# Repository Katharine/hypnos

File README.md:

Project Hypnos
==============

A hardware controller for the Eight Sleep sleep mattress - because controlling your bed with a phone is a pain.

Turn a knob to adjust the temperature, press the knob to turn it on or off, or to turn off the alarm. Simple!

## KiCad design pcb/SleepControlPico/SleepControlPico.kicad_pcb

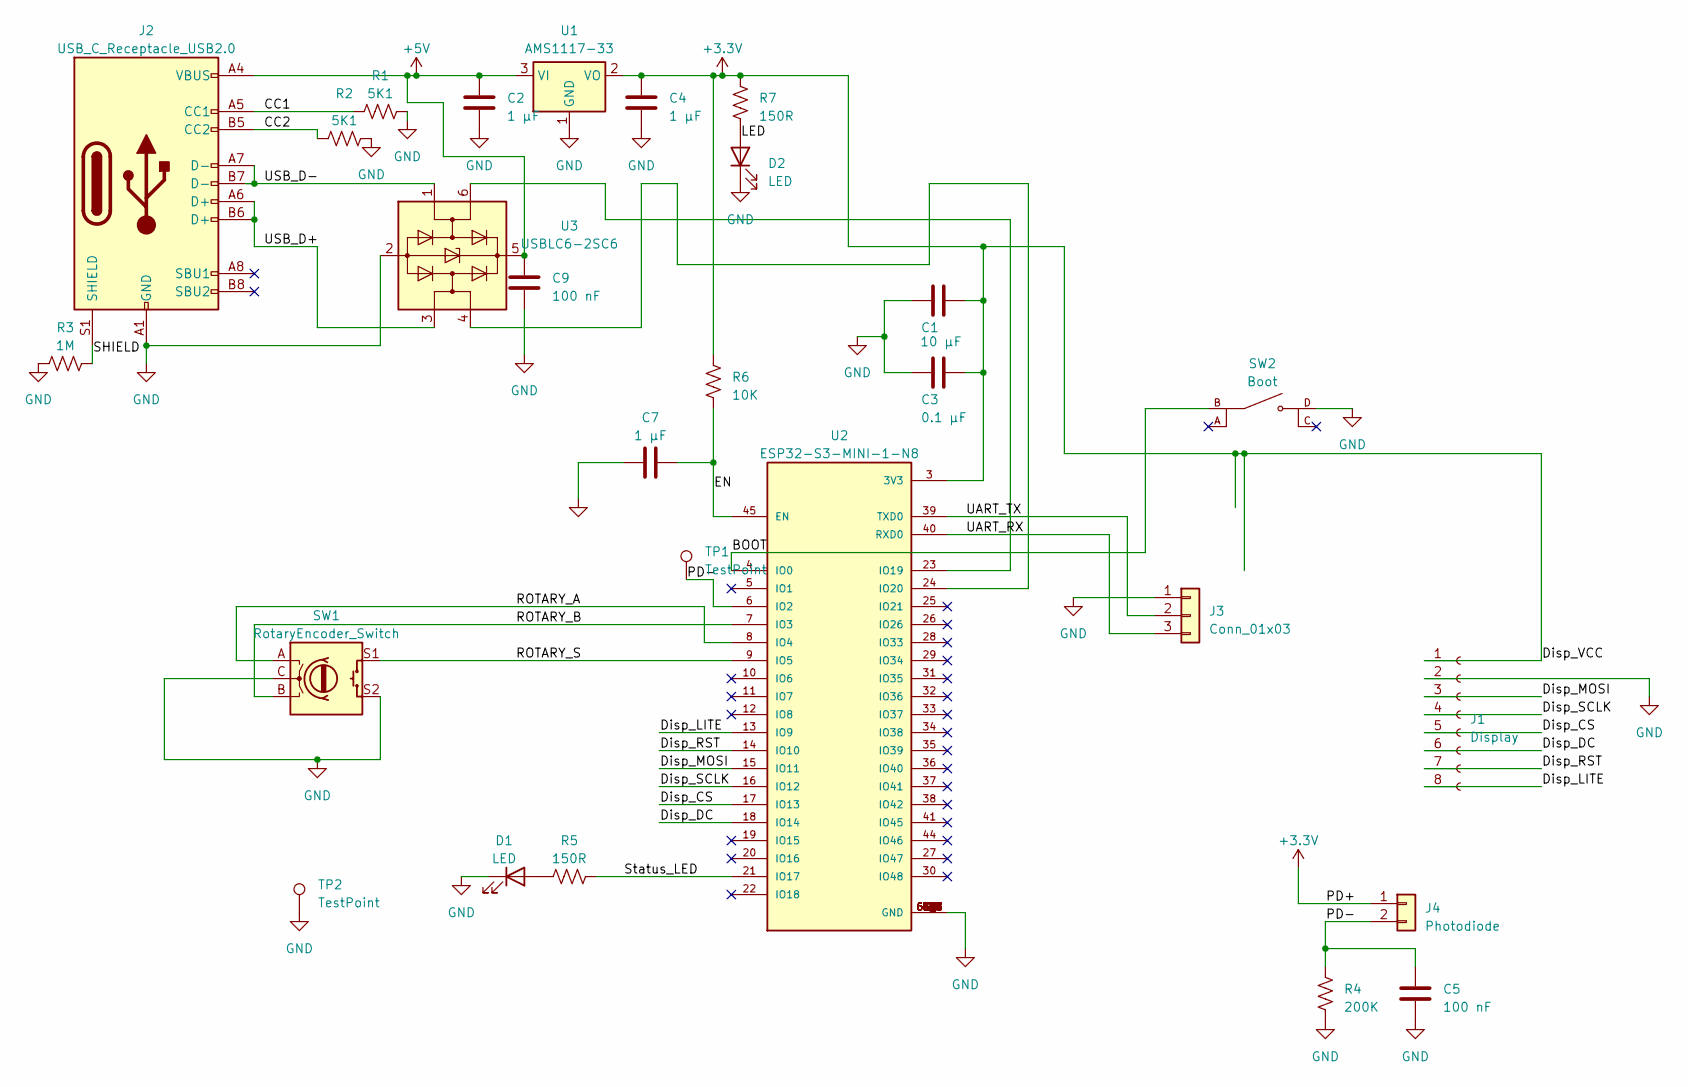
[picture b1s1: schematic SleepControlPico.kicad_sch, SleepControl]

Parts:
C1: 10 µF; C_0603_1608Metric; LCSC Part # C96446
C2, C4, C7: 1 µF; C_0402_1005Metric; LCSC Part # C52923
C3: 0.1 µF; C_0402_1005Metric; LCSC Part # C307331
C5, C9: 100 nF; C_0402_1005Metric; LCSC Part # C307331
D1, D2: LED; LED_0603_1608Metric; LCSC Part # C2286
J1: Display; JST-B8B-ZR-0; LCSC Part # C493145
J2: USB_C_Receptacle_USB2.0; USB_C_Receptacle_G-Switch_GT-USB-7010ASV; LCSC Part # C2988369
J3: Conn_01x03; PinHeader_1x03_P2.54mm_Horizontal; LCSC Part # C2935928
J4: Photodiode; JST_PH_B2B-PH-K_1x02_P2.00mm_Vertical; LCSC Part # C131337
R1, R2: 5K1; R_0603_1608Metric; LCSC Part # C23186
R3: 1M; R_0603_1608Metric; LCSC Part # C22935
R4: 200K; R_Axial_DIN0207_L6.3mm_D2.5mm_P7.62mm_Horizontal; LCSC Part # C58614
R5: 150R; R_0402_1005Metric; LCSC Part # C25133
R6: 10K; R_0603_1608Metric; LCSC Part # C25804
R7: 150R; R_0402_1005Metric; LCSC Part # C25082
SW1: RotaryEncoder_Switch; Bourns-PEC11R-4020F-S0012-MFG; LCSC Part # C143790
SW2: Boot; SW_TS-1187A-B-A-B; PARTREV A0; LCSC Part # C318884
TP1, TP2: TestPoint; TestPoint_Pad_D1.0mm
U1: AMS1117-33; SOT-223-3_TabPin2; LCSC Part # C6186
U2: ESP32-S3-MINI-1-N8; XCVR_ESP32-S3-MINI-1-N8; PARTREV v0.6; LCSC Part # C2913206
U3: USBLC6-2SC6; SOT-23-6; LCSC Part # C7519

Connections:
+3.3V: C1.1, C3.1, C4.1, J1.1, J4.1, R6.1, R7.1, U1.2 (VO), U2.3 (3V3)
+5V: C2.1, C9.2, J2.A4 (VBUS), J2.A9 (VBUS), J2.B4 (VBUS), J2.B9 (VBUS), U1.3 (VI), U3.5 (VBUS)
/BOOT: SW2.B, U2.4 (IO0)
/CC1: J2.A5 (CC1), R1.1
/CC2: J2.B5 (CC2), R2.1
/Disp_CS: J1.5, U2.17 (IO13)
/Disp_DC: J1.6, U2.18 (IO14)
/Disp_LITE: J1.8, U2.13 (IO9)
/Disp_MOSI: J1.3, U2.15 (IO11)
/Disp_RST: J1.7, U2.14 (IO10)
/Disp_SCLK: J1.4, U2.16 (IO12)
/EN: C7.2, R6.2, U2.45 (EN)
/PD-: C5.2, J4.2, R4.1, TP1.1, U2.6 (IO2)
/ROTARY_A: SW1.A, U2.8 (IO4)
/ROTARY_B: SW1.B, U2.7 (IO3)
/ROTARY_S: SW1.S1, U2.9 (IO5)
/SHIELD: J2.S1 (SHIELD), R3.1
/Status_LED: R5.2, U2.21 (IO17)
/UART_RX: J3.3, U2.40 (RXD0)
/UART_TX: J3.2, U2.39 (TXD0)
/USB_D+: J2.A6 (D+), J2.B6 (D+), U3.3 (I/O2)
/USB_D-: J2.A7 (D-), J2.B7 (D-), U3.1 (I/O1)
GND: C1.2, C2.2, C3.2, C4.2, C5.1, C7.1, C9.1, D1.1 (K), D2.1 (K), J1.2, J2.A1 (GND), J2.A12 (GND), J2.B1 (GND), J2.B12 (GND), J3.1, R1.2, R2.2, R3.2, R4.2, SW1.C, SW1.S2, SW2.D, TP2.1, U1.1 (GND), U2.1 (GND), U2.2 (GND), U2.42 (GND), U2.43 (GND), U2.46 (GND), U2.47 (GND), U2.48 (GND), U2.49 (GND), U2.50 (GND), U2.51 (GND), U2.52 (GND), U2.53 (GND), U2.54 (GND), U2.55 (GND), U2.56 (GND), U2.57 (GND), U2.58 (GND), U2.59 (GND), U2.60 (GND), U2.61 (GND), U2.61_1 (GND), U2.61_2 (GND), U2.61_3 (GND), U2.61_4 (GND), U2.61_5 (GND), U2.61_6 (GND), U2.61_7 (GND), U2.61_8 (GND), U2.62 (GND), U2.63 (GND), U2.64 (GND), U2.65 (GND), U3.2 (GND)
unnamed: D1.2 (A), R5.1
unnamed: D2.2 (A), R7.2
unnamed: U2.23 (IO19), U3.6 (I/O1)
unnamed: U2.24 (IO20), U3.4 (I/O2)

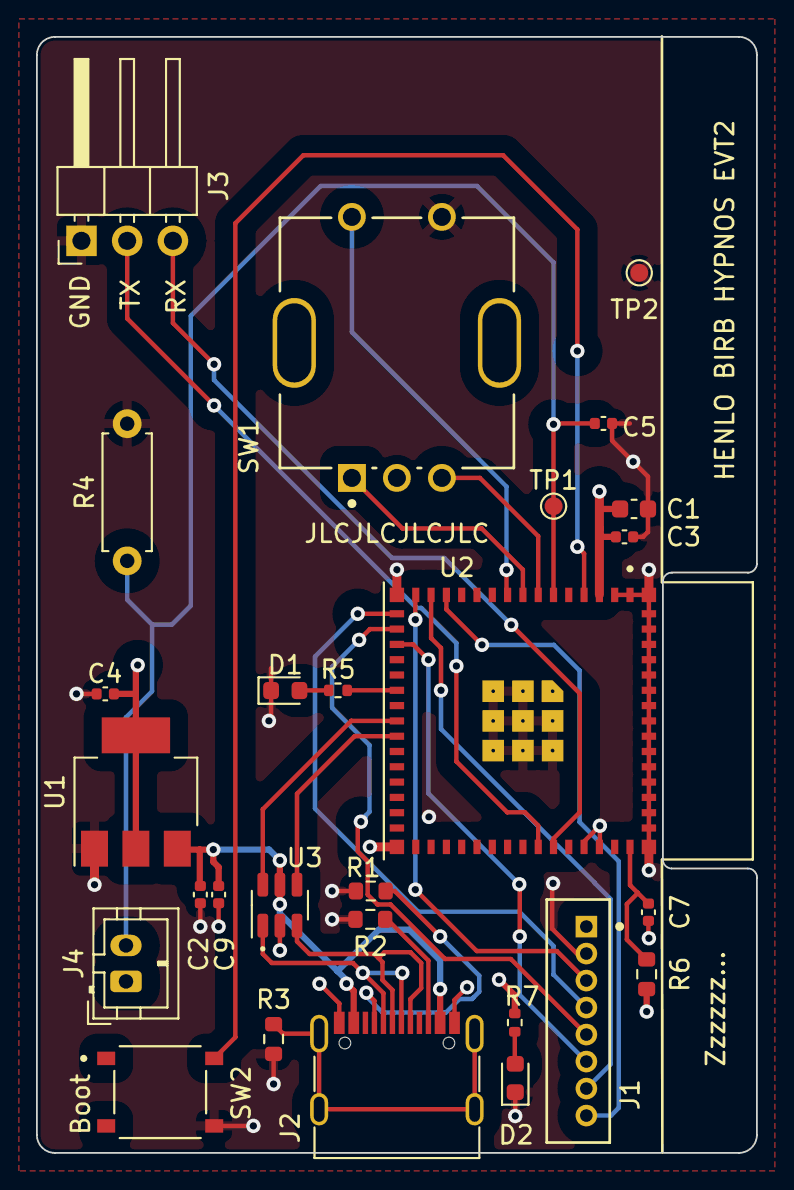
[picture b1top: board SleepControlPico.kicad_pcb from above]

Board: 4 copper layers, 40.0 x 62.0 mm, 27 parts (0 on the bottom side), 27 nets.

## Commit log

2023-02-23 Initial commit. Just screwing around.
    My C++ is so rusty.
2023-02-23 coreback: hand a task off to the other core.
2023-02-23 Lots of refactoring.
    300 lines more code to do exactly the same thing! Woo!
2023-02-24 Use interrupts for spinning the knob.
2023-02-24 Add regular reauth to combat token expiry.
2023-02-28 More messing around.
2023-02-28 Switch to graphical OLED display.
2023-02-28 Add initial PCB draft for posterity
2023-02-28 start over on firmware, now with 100% less arduino
2023-03-03 Adventures in ESP32 land.
2023-03-03 Smaller PCB using an ESP32-S3-MINI-1.
2023-03-05 Enough of the config app to get on the wifi.
2023-03-05 Config works all the way through verified login.
    Revived the Eight Sleep API client from the old Arduino version.
    The mashup of the old and new is not great; more work needed.
    But you can log in! It works!!!
2023-03-05 See if locking LVGL usage stops the verifier from crashing.
2023-03-05 Log in to the thing.
2023-03-06 More stuff.
    - Actually fetch the current bed status
    - A custom, vaguely-animated widget!
    - Bigger (2 MB) app partitions, because we're out of space.
    - OTA partitions. We need an 8 MB flash between these changes.
2023-03-07 Incredibly basic backlight control.
    Using a phototransistor (currently set up in a voltage divider with a
    200 kΩ resistor on pin 6), pick some numbers based on the voltage
    picked up by the ADC (and blast to 100% if it's saturated).
    Also manually reset the screen on boot. You'd think esp_lcd_panel_reset
    would do that, but it doesn't.
2023-03-07 Improve backlight behaviour in borderline cases.
2023-03-07 Pretend to control your bed!
    - Fetches and maintains actual bed state from the internet
    - Lets you spin the knob (to no avail)
    - Snaps display back to real targets if they change
    - Regularly reauths and updates bed state.
2023-03-07 Backlight tweaking.
2023-03-08 Zero is neither positive nor negative.
2023-03-08 Fix the time log under newlib-nano.
2023-03-08 Now actually controls the real bed!
2023-03-08 Added alarm mode, where you can turn off active alarms.
2023-03-08 Use the modern API, so we stay in "smart" mode.
2023-03-10 fix some bugs
2023-03-10 add tiny PCB to attach the photodiode
2023-03-11 Final-ish PCB layout
2023-03-11 remove accelerometer (out of stock)
2023-03-11 Final(?) PCB revision.
2023-03-11 Add onshape link
2023-03-11 Try to fix the state thread sometimes getting wedged.
2023-03-12 Add tick marks to the main UI.
    Tick marks indicate:
    - The current target
    - The bed's current target, if it's different
    - The bed's actual temperature
    Also some bug fixes that caused the actual temperature to be wrong.
2023-03-12 Try to fix bug where phone doesn't realise OOBE finished.
2023-03-13 add sdkconfig
2023-03-14 Add the gitignores
2023-03-16 Start putting together a long-press menu. It sucks.
2023-03-17 Pull out a screen stack.
    Instead of explicitly managing screens and groups everywhere always,
    have a stack of screens that can be pushed, popped, or replaced.
    As part of this, the shared_ptrs to all the common parts have been
    extracted into some statics that everything can freely reference.
2023-03-18 Move statics out of statics class.
2023-03-18 Turn down the dimmest backlight level.
2023-03-18 Fix screenstack not popping properly.
    When `Stack::pop` was called, a copy of the newly-revealed screen would
    be added to the stack. When it was called again, the active screen
    would be destroyed, but then replaced with itself - resulting in just
    showing a blank screen.
    Fix the behaviour by not pushing the screen on to the stack a second time.
2023-03-18 Add confirmation prompts to menu actions.
    The "Reboot" and "Factory Reset" menu options now both have a
    confirmation prompt.
2023-03-18 Fix the menu having a different coloured background.
2023-03-27 update config to reflect real board setup
2023-03-27 Fix wrong resistor part
2023-03-27 Fix USB D+ and D- lines being switched
